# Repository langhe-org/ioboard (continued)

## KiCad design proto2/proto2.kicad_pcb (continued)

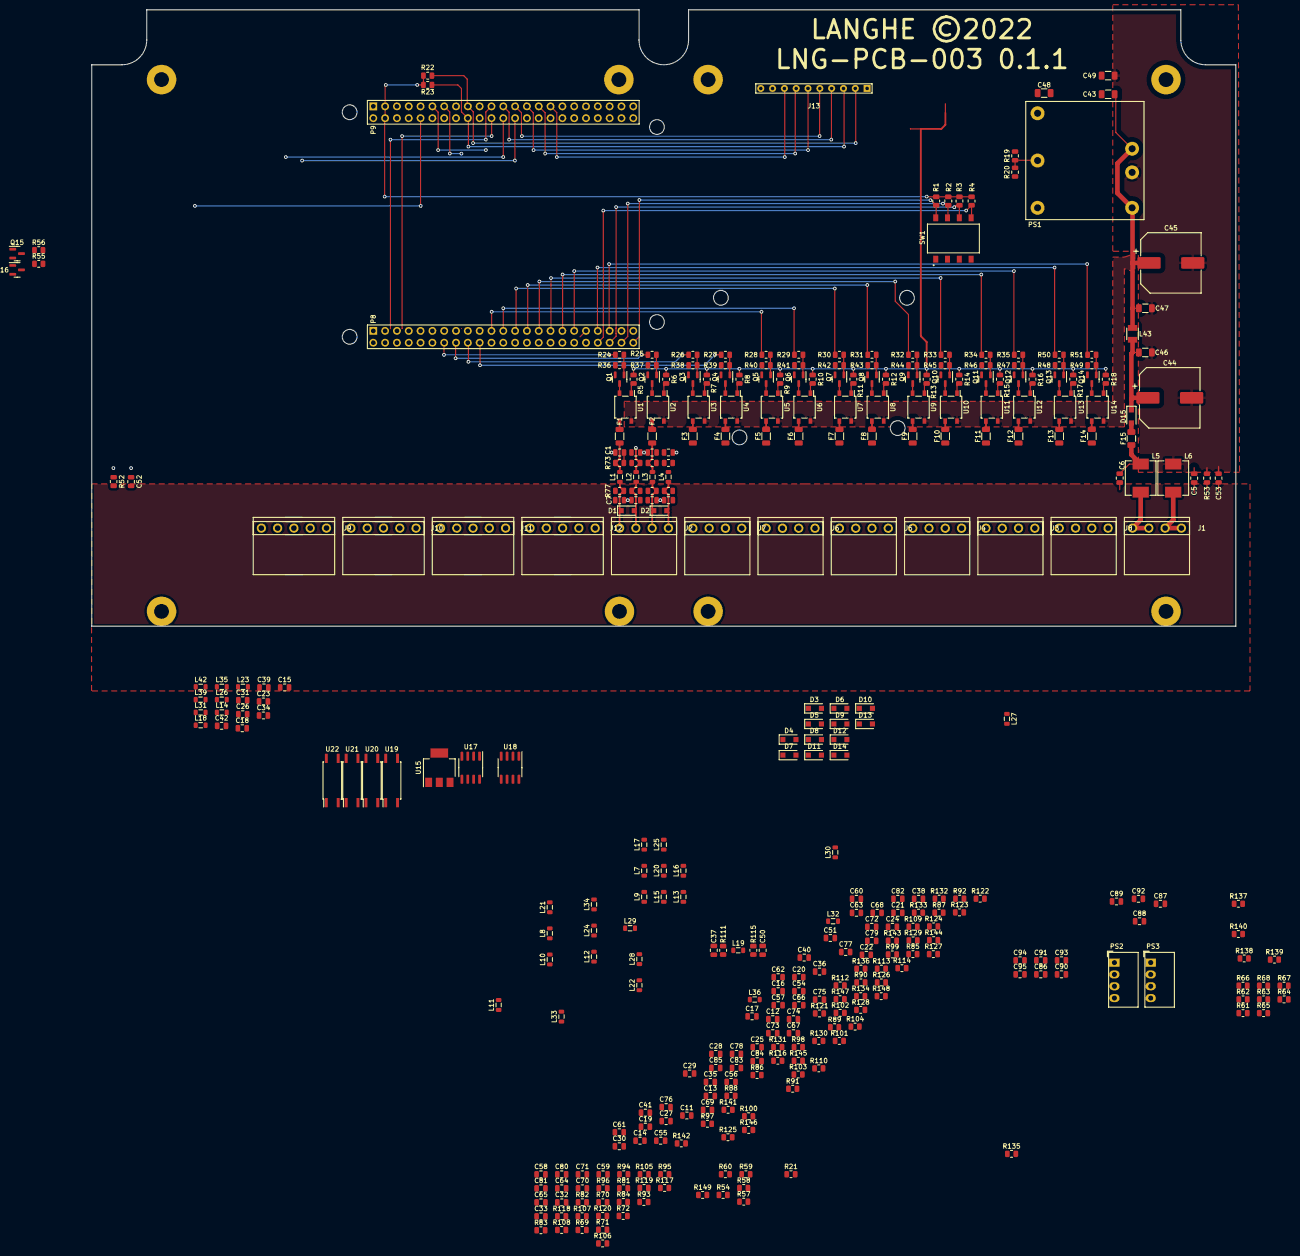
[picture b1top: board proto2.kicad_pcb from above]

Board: 4 copper layers, 245.9 x 132.5 mm, 369 parts (0 on the bottom side), 250 nets.

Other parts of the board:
Outline: Polycase_DC96

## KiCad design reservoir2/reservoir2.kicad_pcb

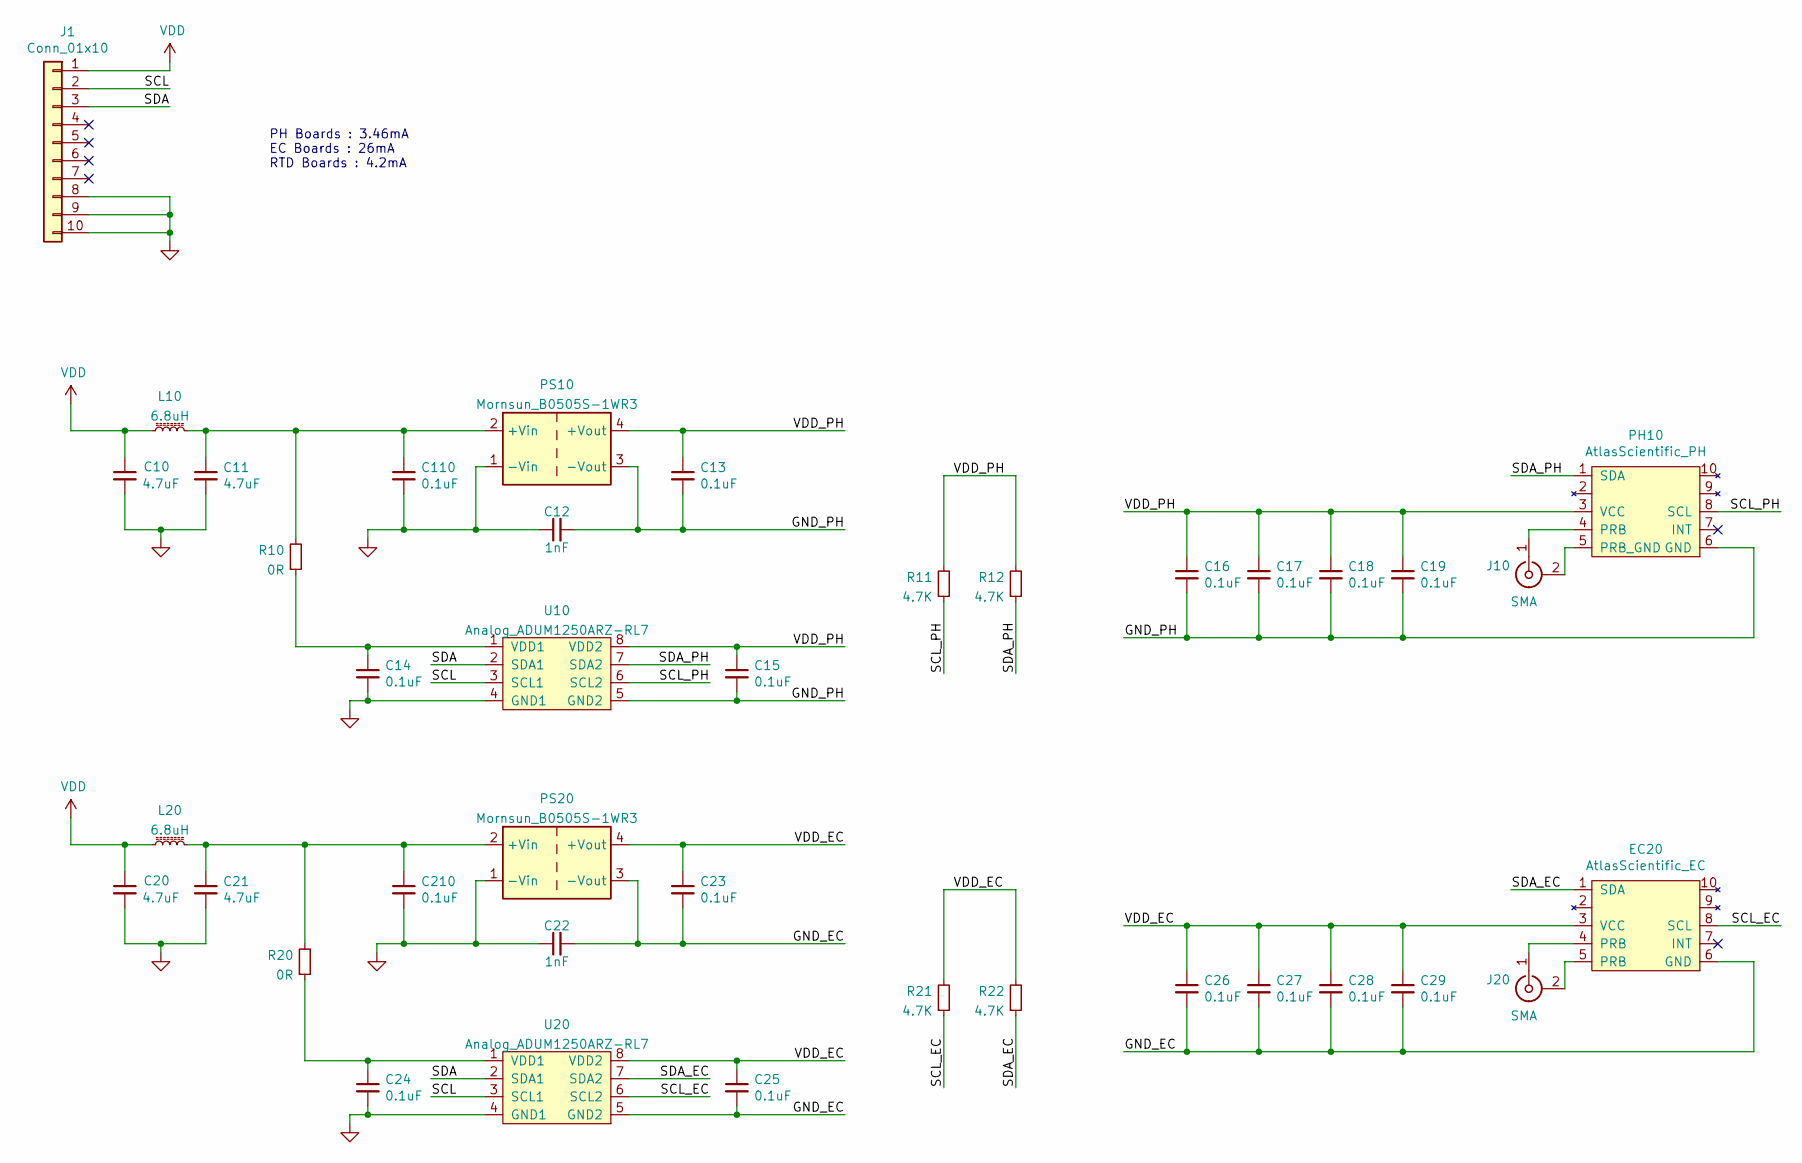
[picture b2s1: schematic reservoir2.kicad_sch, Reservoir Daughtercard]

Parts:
C10, C11, C20, C21: 4.7uF; C_0805_2012Metric; LCSC C49678
C12, C22: 1nF; C_0805_2012Metric; LCSC C49678
C13, C14, C15, C16, C17, C18, C19, C23, C24, C25, C26, C27, C28, C29, C110, C210: 0.1uF; C_0805_2012Metric; LCSC C49678
EC20: AtlasScientific_EC; AtlasScientific_OEM
J1: Conn_01x10; Proto2_DaughterCard
J10, J20: SMA; SMA_EdgeMount
L10, L20: 6.8uH; L_0805_2012Metric; PartNumber MLZ2012N6R8LT000; LCSC C82157
PH10: AtlasScientific_PH; AtlasScientific_OEM
PS10, PS20: Mornsun_B0505S-1WR3; LCSC C131038
R10, R20: 0R; R_0805_2012Metric; LCSC C17477
R11, R12, R21, R22: 4.7K; R_0805_2012Metric; LCSC C17673
U10, U20: Analog_ADUM1250ARZ-RL7; SOIC-8_3.9x4.9mm_P1.27mm; LCSC C13839

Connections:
/GND_EC: C22.2, C23.2, C25.2, C26.2, C27.2, C28.2, C29.2, EC20.6 (GND), PS20.3 (-Vout), U20.5 (GND2)
/GND_PH: C12.2, C13.2, C15.2, C16.2, C17.2, C18.2, C19.2, PH10.6 (GND), PS10.3 (-Vout), U10.5 (GND2)
/SCL: J1.2, U10.3 (SCL1), U20.3 (SCL1)
/SCL_EC: EC20.8 (SCL), R21.1, U20.6 (SCL2)
/SCL_PH: PH10.8 (SCL), R11.1, U10.6 (SCL2)
/SDA: J1.3, U10.2 (SDA1), U20.2 (SDA1)
/SDA_EC: EC20.1 (SDA), R22.1, U20.7 (SDA2)
/SDA_PH: PH10.1 (SDA), R12.1, U10.7 (SDA2)
/VDD_EC: C23.1, C25.1, C26.1, C27.1, C28.1, C29.1, EC20.3 (VCC), PS20.4 (+Vout), R21.2, R22.2, U20.8 (VDD2)
/VDD_PH: C13.1, C15.1, C16.1, C17.1, C18.1, C19.1, PH10.3 (VCC), PS10.4 (+Vout), R11.2, R12.2, U10.8 (VDD2)
GND: C10.2, C11.2, C12.1, C14.2, C20.2, C21.2, C22.1, C24.2, C110.2, C210.2, J1.8, J1.9, J1.10, PS10.1 (-Vin), PS20.1 (-Vin), U10.4 (GND1), U20.4 (GND1)
unnamed: C11.1, C110.1, L10.2, PS10.2 (+Vin), R10.2
unnamed: C14.1, R10.1, U10.1 (VDD1)
unnamed: C21.1, C210.1, L20.2, PS20.2 (+Vin), R20.2
unnamed: C24.1, R20.1, U20.1 (VDD1)
unnamed: EC20.4 (PRB), J20.1 (In)
unnamed: EC20.5 (PRB), J20.2 (Ext)
unnamed: J10.1 (In), PH10.4 (PRB)
unnamed: J10.2 (Ext), PH10.5 (PRB_GND)
VDD: C10.1, C20.1, J1.1, L10.1, L20.1

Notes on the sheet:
PH Boards : 3.46mA EC Boards : 26mA RTD Boards : 4.2mA

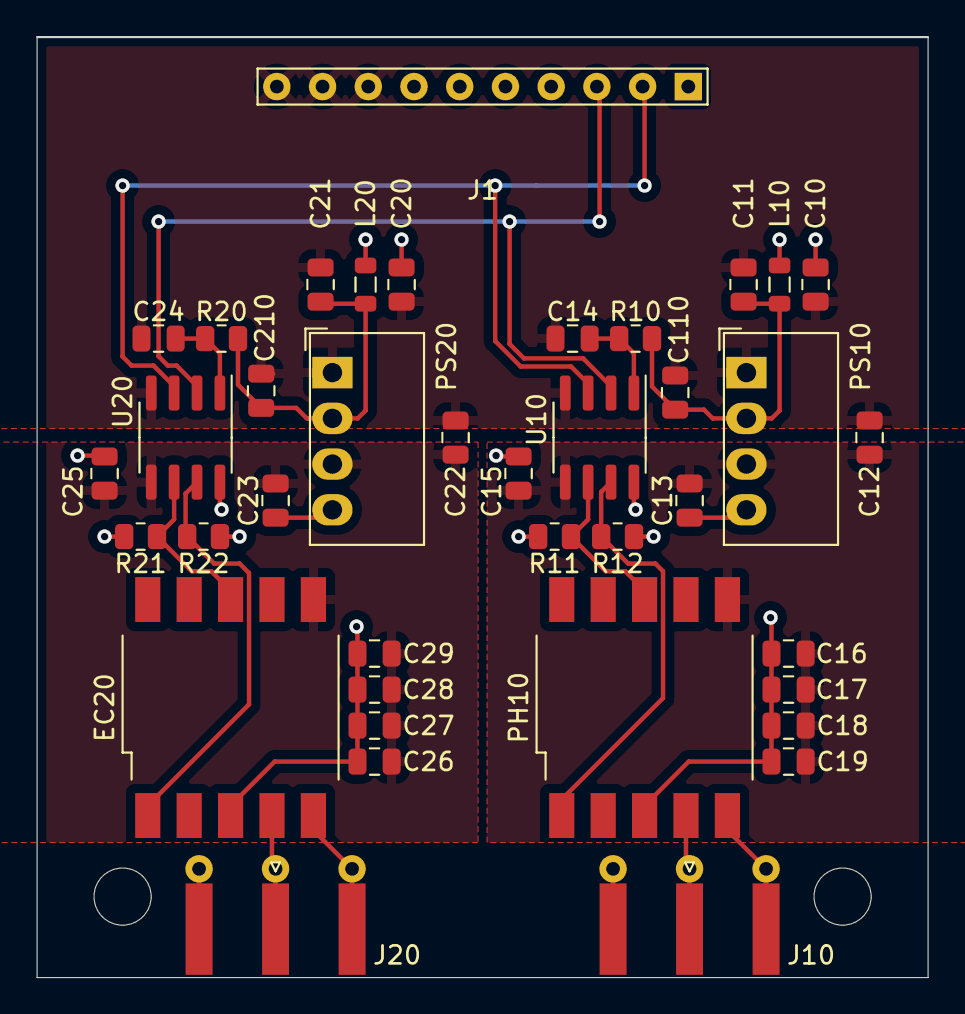
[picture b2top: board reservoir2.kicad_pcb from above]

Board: 2 copper layers, 49.5 x 52.2 mm, 39 parts (0 on the bottom side), 20 nets.

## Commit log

2021-12-10 Add initial work to repository.
2021-12-15 Routed Board.
2021-12-16 Added correct cap and moved DIP switches.
2021-12-17 Finished routing board and other changes, bad commit message, I know.
2021-12-17 Added manufacturing outputs to ignore.
2021-12-18 Reversed the filter order.
2021-12-19 Updated filters and Power supply foorptint.
2021-12-21 Added note for current draw of SBCs.
2021-12-21 Updated drill hole sizes.
2021-12-23 Fixing the issues the filter-fix merge created.
2021-12-23 Removed silkscreen outlines fro BBB and RPi.
2021-12-24 Added schematics following Atlas Scientific's recomended design.
2021-12-24 Added MOSFET drivers for the SSRs, pullups for I2C, and referenced DIP switches to 3V3.
2021-12-24 Removed Raspberry Pi, added spacing to terminals.
2021-12-28 Replaced LDO with a D2PAK type. Cleaned some traces.
2021-12-30 Removed UART board.
2021-12-30 Added reverse polarity diode.
2021-12-30 Created new board design for connected grounds.
2021-12-30 New adapter for RPi to BBB boards.
2021-12-30 Updates and changes for production run of 0.1.0
2022-01-13 Replaced 2N7000 symbol with 2N7002.
2022-01-14 Replaces board outline with Polycase DC-96 outline.
2022-01-20 Conversion to 6.0 and some minor updates.
2022-01-20 Added KiCad 6.0 local project file.
2022-01-21 Removed sym-lib-table file. Not sure how it got there.
2022-01-21 Changed some design rule severities.
2022-01-21 Added another 2 outputs and re-routed board.
2022-01-28 Added Datasheet links
2022-01-29 Removed KiCad 5.1 Files
2022-02-02 Added switch for 5V external devices power based off SYS_RESETn.
2022-02-17 Working in suggestions from CFL review.
2022-02-17 Reworked board for just one reservoir with isolators and removed temperature.
2022-02-17 Changes suggested by CFL.
2022-02-22 Moved reservoir2 to it's own repo and archived rpiadapt2.
2022-02-23 Laying out new filters and some schematic updates.
2022-02-24 Laying out board. in-process commit.
2022-03-02 Filter layout and some schematic fixes.
2022-03-07 Final layout for 0.2.0 and various BOM and minor schematic updates.
2022-03-07 Fixed SSR footprint in schematic and corrected output pinout.
2022-05-30 Rearranged GPIO around the boot pins.
2022-05-30 Moved the board outline so there is more room for connectors. Moved connectors so vertical plugs can be used.
2022-06-07 Added larger fuse for 24V, replaced main polarity diode, and relayed out board to fit new components.
2022-06-08 Added Kicad 6.0 files and *-backups/ folders to the ignore.
2022-06-08 Updated PTC sizes so they will not trip with typical current draw.
2022-07-26 Changed revision on schematic to 0.3.0.
2022-07-26 Changed board outline to Ploycase WH-16 and revision to 0.3.0.
2022-08-04 Updated part number for F15 and D15.
2022-08-04 Updated F15,D15,U1-14 to parts in stock at JLC. Updated U1-14 footprints to more common size.
2022-09-19 Rerouting outputs, adding integrated analog input.
2023-05-20 Removed some old backups and files from older Kicad versions
2023-05-20 Added license
2023-05-20 Converted files to Kicad v7.0.2
2023-05-20 Changed paper size and some text on the titleblocks
2023-05-20 Removed part number from board
2023-05-20 Changed internal references from proto2 to ioboard
2023-05-20 Ranamed files from proto2 to ioboard
2023-05-20 Renamed directory from proto2 to ioboard
2023-05-22 Filled in the readme
